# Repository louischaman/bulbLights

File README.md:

DMX controlled incandescent bulb dimmers.

# Requirements
- Arduino IDE (test v1.8.1)
- ISP programmer (I'm using a USBTinyISP)
- [Sparkfun ISP Pogo Adapter](https://www.sparkfun.com/products/11591)

# Running the hardware test
1. Make sure correct fuse settings are flashed (easily done by flashing an arduino nano bootloader?)
1. Use ```./tests/bulbLightHardwareTest.ino.hex``` or build in the IDE and use the hex file with the same name.
1. Flash with avrdude
    - Linux: ```./scripts/flash_firmware.sh`` can be used.
    - Windows: See [Adafruit tutorial](https://learn.adafruit.com/usbtinyisp/avrdude). Use same settings as in above script.

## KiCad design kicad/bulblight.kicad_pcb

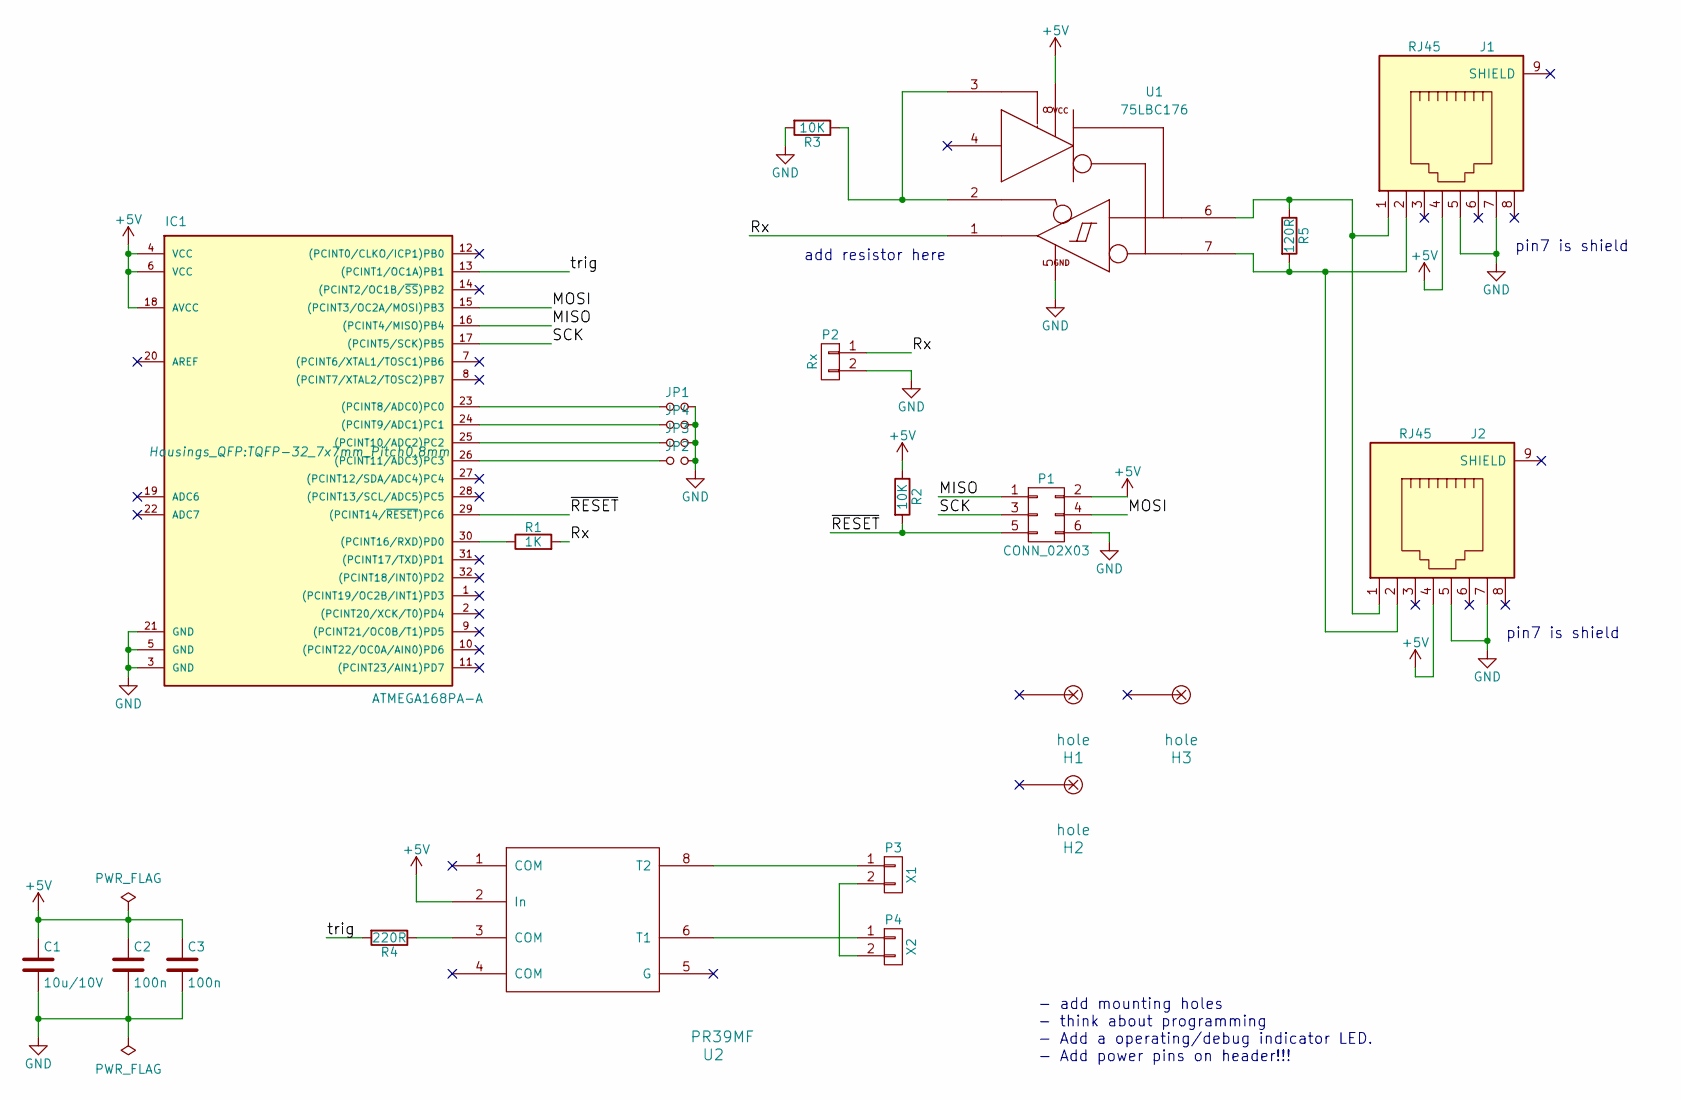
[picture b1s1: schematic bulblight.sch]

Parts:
C1: 10u/10V; C_0805
C2, C3: 100n; C_0603
H1, H2, H3: hole; MountingHole_4.3mm_M4_ISO7380_Pad
IC1: ATMEGA168PA-A; TQFP-32_7x7mm_Pitch0.8mm
J1, J2: RJ45; RJ45_8
JP1, JP2, JP3, JP4: Jumper_NO_Small; C_0805_HandSoldering
P1: CONN_02X03; Pin_Header_Straight_2x03
P2: Rx; Pin_Header_Straight_1x02
P3: X1; euroTerminal
P4: X2; euroTerminal
R1: 1K; R_0603
R2, R3: 10K; R_0603
R4: 220R; R_0603
R5: 120R; R_0603
U1: 75LBC176; SOIC-8_3.9x4.9mm_Pitch1.27mm
U2: PR39MF; SMD8

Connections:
+5V: C1.1, C2.1, C3.1, IC1.4 (VCC), IC1.6 (VCC), IC1.18 (AVCC), J1.4, J2.4, P1.2, R2.1, U1.8 (VCC), U2.2 (In)
/MISO: IC1.16 ((PCINT4/MISO)PB4), P1.1
/MOSI: IC1.15 ((PCINT3/OC2A/MOSI)PB3), P1.4
/Rx: P2.1, R1.2, U1.1 (ROUT)
/SCK: IC1.17 ((PCINT5/SCK)PB5), P1.3
/trig: IC1.13 ((PCINT1/OC1A)PB1), R4.2
/~RESET: IC1.29 ((PCINT14/~RESET~)PC6), P1.5, R2.2
GND: C1.2, C2.2, C3.2, IC1.3 (GND), IC1.5 (GND), IC1.21 (GND), J1.5, J1.7, J2.5, J2.7, JP1.2, JP2.2, JP3.2, JP4.2, P1.6, P2.2, R3.2, U1.5 (GND)
unnamed: IC1.23 ((PCINT8/ADC0)PC0), JP1.1
unnamed: IC1.24 ((PCINT9/ADC1)PC1), JP4.1
unnamed: IC1.25 ((PCINT10/ADC2)PC2), JP3.1
unnamed: IC1.26 ((PCINT11/ADC3)PC3), JP2.1
unnamed: IC1.30 ((PCINT16/RXD)PD0), R1.1
unnamed: J1.1, J2.1, R5.1, U1.6 (BUS+)
unnamed: J1.2, J2.2, R5.2, U1.7 (BUS-)
unnamed: P3.1, U2.8 (T2)
unnamed: P3.2, P4.2
unnamed: P4.1, U2.6 (T1)
unnamed: R3.1, U1.2 (/RE), U1.3 (DE)
unnamed: R4.1, U2.3 (COM)

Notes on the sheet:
pin7 is shield
- add mounting holes - think about programming - Add a operating/debug indicator LED. - Add power pins on header!!!
add resistor here

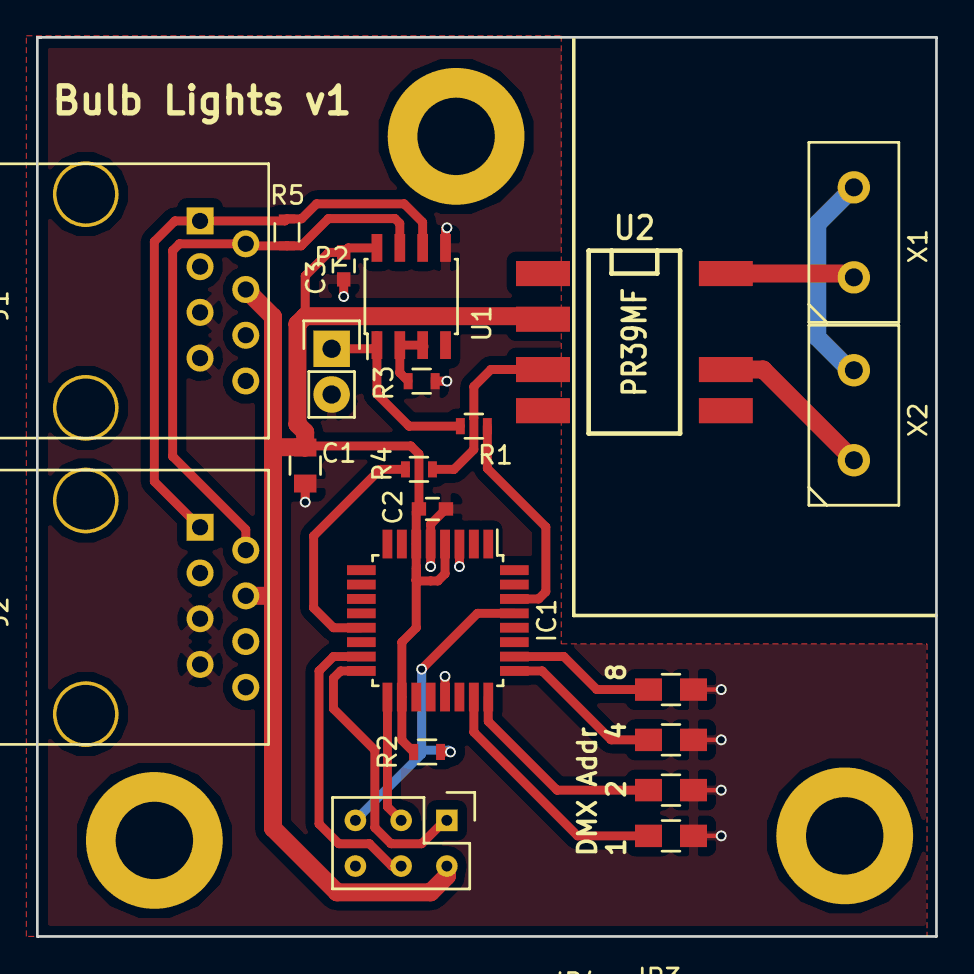
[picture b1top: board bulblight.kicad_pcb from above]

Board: 2 copper layers, 49.9 x 49.9 mm, 24 parts (0 on the bottom side), 20 nets.

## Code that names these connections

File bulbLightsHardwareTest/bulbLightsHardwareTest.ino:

/**
 * Test of various parts needed for the bulb lights.
 * 
 * Prototype:
 * - ATMega328p
 * - Vcc = 3.3-5 V
 * - F_CPU = 8 MHz
 * 
 * | Test       | Method
 * | --------   | ------
 * | Triac      | Connect bulb and set triac pin. NOTE! Mains voltages! Probably should do this separately
 * | DMX input  | Connect DMX source and check for activity.
 * | Addr pins  | Print address somewhere?
 */

// Global constants
// This is the base address of the device. It is used as an offset and is added to the value
// of the address pins to calculate the device address (addr).
// Should be set in the form 0xh0 and should never exceed 0xf0 in order to avoid overflowing
// the uint8_t containing the address.
static constexpr uint8_t baseAddr = 0;
static_assert(0xf0 >= baseAddr, "baseAddr is greater than 0xf0");  // assert that baseAddr is < 0xf0.

// pindefs
static constexpr uint8_t triacPin = PB1;
static constexpr uint8_t addrPin0 = PC0;
static constexpr uint8_t addrPin1 = PC1;
static constexpr uint8_t addrPin2 = PC2;
static constexpr uint8_t addrPin3 = PC3;

// global variables
static uint8_t addr = 0x00; // no address set yet.

// Bulb control functions
// triac triggers when pin is low
static inline void setTrigger() {
    // set low.
    PORTB &= ~(1 << triacPin);
}
static inline void clearTrigger() {
    // set high.
    PORTB |= (1 << triacPin);
}
static inline void toggleTrigger() {
    PINB |= (1 << triacPin);
}
static inline bool isTrigger() {
    return (bool)(PINB & (1 << triacPin));
}

// DMX functions
// Check the value of the pins.
static inline uint8_t checkAddrPins() {
    // The address is set by reading the first 4 pins of register C.
    return (0x0f & PINC);
}

void setup() {
    // put your setup code here, to run once:
    Serial.println(F("Setup..."));
    // Setup triac pin to off state first
    DDRB |= (1 << triacPin); // set to output
    clearTrigger();
    
    // TODO dmx
    addr = baseAddr + checkAddrPins();
    Serial.print(F("Addr: "));
    Serial.println(addr);

    Serial.println(F("Setup Done"));
}

void loop() {
    // put your main code here, to run repeatedly:
    toggleTrigger();
    Serial.print(F("Trig: "));
    Serial.println(isTrigger());
    Serial.println();
    delay(500);
}

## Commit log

2017-04-22 Creating repo
2017-04-22 Added readme and programming scripts
